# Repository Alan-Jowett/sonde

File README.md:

<!-- SPDX-License-Identifier: MIT
  Copyright (c) 2026 sonde contributors -->

# Sonde

**A programmable sensor platform with desired-state convergence from cloud to node.**

Sonde turns battery-powered sensor nodes into programmable probes that keep static firmware but execute dynamic behavior defined by verified BPF programs ([RFC 9669](https://www.rfc-editor.org/rfc/rfc9669.html)). The gateway owns radio-facing orchestration; an external control plane owns fleet intent. Together they converge node state by flowing **desired state** down to the gateway and **actual state / application data** back upstream.

Nodes never need feature-driven firmware updates for normal application changes. New sampling logic, thresholds, diagnostics, and routing behavior ship as verified BPF plus gateway-managed state changes. The reference implementation targets ESP32-C3/S3 nodes and modems, with a cloud-agnostic connector model and an Azure reference deployment in this repository.

> **Status:** Active development, pre-1.0. The workspace includes the core protocol/gateway/node/modem stack, admin tooling, pairing surfaces, example handlers, and Azure companion/handler components. See [Project status](#project-status) below.

> ⚠️ **Spec-first project** — edit the [specification documents](docs/) before changing code. Code modules may be regenerated from specs. See [Contributing](docs/contributing.md#spec-first-development-model).

---

## Project status

**Lifecycle:** Active development — pre-1.0. APIs and wire formats may change between commits. Not yet recommended for production deployments.

**Maintenance:** The project is actively maintained. Bug reports, pull requests, and feature discussions are welcome. See [Contributing](docs/contributing.md) for guidelines.

**Versioning:** The project has not yet reached v1.0. Breaking changes to the wire protocol, connector schema, or crate APIs may still occur.

**Current repository shape:** the workspace already spans the device runtime, the gateway runtime, local admin/pairing tools, and cloud-facing integration surfaces.

| Component | Purpose |
|---|---|
| [`sonde-protocol`](crates/sonde-protocol) | Shared `no_std` wire format, CBOR message types, program-image encoding, and crypto abstractions |
| [`sonde-gateway`](crates/sonde-gateway) | Async gateway service: node sessions, program distribution, reconciliation hooks, connector I/O, and gRPC admin |
| [`sonde-node`](crates/sonde-node) | ESP32-C3/S3 firmware: wake cycle, BPF execution, persistent state, and radio protocol |
| [`sonde-modem`](crates/sonde-modem) | ESP32-S3 bridge between ESP-NOW radio and the gateway |
| [`sonde-admin`](crates/sonde-admin) | CLI for gateway administration and pairing flows |
| [`sonde-bpf`](crates/sonde-bpf) | Safe BPF interpreter used by the node runtime |
| [`sonde-pair`](crates/sonde-pair) + [`sonde-pair-ui`](crates/sonde-pair-ui/src-tauri) | BLE pairing core plus Tauri desktop/Android UI |
| [`sonde-azure-companion`](crates/sonde-azure-companion) | Reference connector/runtime bridge for Azure-backed control-plane sync |
| [`sonde-azure-handler`](crates/sonde-azure-handler) | Azure cloud-side reconciliation and data-ingest component |
| [`sonde-tmp102-handler`](crates/sonde-tmp102-handler) / [`sonde-sht40-handler`](crates/sonde-sht40-handler) | Example application handlers |
| [`sonde-e2e`](crates/sonde-e2e) | End-to-end validation harness |

CI runs on every push and PR and covers workspace build/test flows plus target-specific firmware and UI pipelines.

---

## How it works

```
┌───────────────────────────┐
│   Control plane / cloud   │
│ desired state, analytics, │
│ fleet policy, app ingest  │
└─────────────┬─────────────┘
              │ DESIRED_STATE / ACTUAL_STATE / APP_DATA
┌─────────────▼─────────────┐     local IPC      ┌──────────┐     USB      ┌──────────┐   ESP-NOW   ┌──────────┐
│ Connector / companion     │◄──────────────────►│ Gateway  │◄────────────►│  Modem   │◄───────────►│   Node   │
│ transport adapter         │                    │          │               │          │              │  BPF VM  │
└───────────────────────────┘                    └──────────┘               └──────────┘              └──────────┘
```

1. **The control plane declares intent** as complete desired state for one gateway or node at a time.
2. **A connector/companion transports that intent** to the gateway over the local connector API. The connector is cloud-agnostic; it adapts some external store-and-forward transport to Sonde's framed connector messages.
3. **Nodes wake on their own schedule** and send `WAKE` over ESP-NOW. Communication is always node-initiated.
4. **The gateway reconciles actual vs. desired state** at wake time, then responds with the next action: continue, update resident program, queue an ephemeral diagnostic, change schedule, rotate state, or reboot.
5. **The node executes its resident BPF program**, updates persistent maps, and emits application data when needed.
6. **The gateway publishes upstream actual state and app data** so the control plane can observe convergence and decide the next desired state.

The firmware never embeds application-specific policy. It provides the execution and transport substrate; BPF plus desired-state convergence define behavior.

---

## Architecture

The design separates five concerns:

| Layer | Lifetime | Location |
|---|---|---|
| **Firmware** | Static, uniform across all nodes | Flash |
| **Program logic** | Dynamic, delivered as BPF bytecode | Flash (resident) or RAM (ephemeral) |
| **Persistent state** | Survives deep sleep | Sleep-persistent memory |
| **Gateway runtime** | Always-on edge service | Gateway host |
| **Control plane** | External desired-state authority | Cloud or other upstream system |

This gives Sonde OTA-like flexibility without turning firmware rollout into the main application-delivery mechanism. New sensors, thresholds, schedules, diagnostics, and cloud-side routing changes are expressed as BPF programs plus desired state.

### Desired-state convergence

The connector protocol is organized around four message families:

- **`DESIRED_STATE`** — control plane to gateway, carrying complete desired state for one gateway or node.
- **`ACTUAL_STATE`** — gateway to control plane, carrying the latest observed gateway or node state.
- **`APP_DATA`** — gateway to control plane, carrying node-originated application payloads.
- **`CONNECTOR_HEALTH`** — gateway to control plane, carrying connector session health.

This makes the gateway the convergence engine at the edge: it accepts desired state from upstream, waits for node-initiated contact, applies the necessary changes, and reports the resulting actual state back upstream.

### Reference cloud deployment

This repository's reference cloud path is Azure-based:

- `sonde-azure-companion` bridges the gateway's local admin/connector surfaces to Azure runtime services.
- `sonde-azure-handler` consumes upstream connector traffic, stores actual state and sensor data, and emits downstream desired state.

The connector model itself is not Azure-specific, so other control-plane transports can implement the same gateway-facing contract.

---

## BPF programs

Nodes execute [BPF programs](docs/bpf-environment.md) that define all application behavior. Two classes exist:

- **Resident** — stored in flash, runs every wake cycle, full map read/write access.
- **Ephemeral** — one-shot diagnostic, stored in RAM, read-only maps, discarded after execution.

Programs are compiled to BPF ELF, verified by [Prevail](https://github.com/vbpf/ebpf-verifier) on the gateway, and distributed over the air. See the [BPF environment](docs/bpf-environment.md) doc for the full helper API, memory model, verification profiles, and development workflow.

---

## Radio protocol and security

Communication is always **node-initiated**. The gateway never wakes a node. Each radio frame uses:

- a fixed **11-byte binary header** (`key_hint`, `msg_type`, `nonce`),
- a CBOR payload encrypted with **AES-256-GCM**, and
- a 16-byte GCM authentication tag.

The header is authenticated as AEAD additional data; the payload is both encrypted and authenticated. Nodes and gateways use unique per-node 256-bit pre-shared keys. `WAKE` uses a random nonce; follow-on traffic uses gateway-assigned sequence numbers for replay protection.

The basic edge loop is still: node sends `WAKE` → gateway responds with `COMMAND` → node executes BPF → node sleeps. Programs are distributed via a node-driven chunked transfer. Application data flows as `APP_DATA`, with `APP_DATA_REPLY` used for request/response helper calls.

See [protocol.md](docs/protocol.md) for the full wire format and [security.md](docs/security.md) for the trust model.

### Security model

- Each node has a unique 256-bit pre-shared key stored in a dedicated flash partition.
- Keys are provisioned via USB-mediated pairing; no over-the-air key exchange.
- The gateway stores the key database and authenticates/decrypts all radio traffic with AES-256-GCM.
- Nonces provide replay protection for WAKE; gateway-assigned sequence numbers protect all subsequent messages.
- BPF programs are integrity-checked by content hash at every transfer.
- Nodes can be factory-reset (erasing key, maps, and program) and re-paired with a fresh identity.

See [security.md](docs/security.md) for the complete security model: threat model, key provisioning, authentication, replay protection, identity binding, failure modes, and gateway failover.

---

## BPF program environment

BPF programs have access to raw bus primitives (I2C, SPI, GPIO, ADC), communication helpers (`send`, `send_recv`), persistent maps, and system functions. The firmware provides bus access; sensor-specific protocols live in the BPF program. See [bpf-environment.md](docs/bpf-environment.md) for the full helper API, memory model, verification profiles, and development workflow.

---

## Application handlers

The gateway is a platform service — application logic runs in a separate **handler process**. When a BPF program calls `send()` or `send_recv()`, the gateway forwards the data to the handler via stdin (length-prefixed CBOR). The handler processes it and replies via stdout. Handlers are routed by `program_hash`, so different BPF programs can have different handlers.

The developer ships two artifacts: a **BPF ELF** (node-side) and a **handler** in any language (gateway-side). See [gateway-api.md](docs/gateway-api.md) for the full handler protocol, message format, and examples.

---

## Operational concerns

- **Gateway failover** — replace the gateway with another instance provisioned with the same key database. Nodes won't notice.
- **Development** — BPF programs are platform-agnostic. Compile, verify, and test locally with `libsonde_test` — no hardware needed.
- **Diagnostics** — push an ephemeral program to inspect node state without disturbing the resident program.
- **Firmware updates** — physical access only. By design, firmware changes are rare — new features ship as BPF programs.

See [gateway-requirements.md](docs/gateway-requirements.md) and [node-requirements.md](docs/node-requirements.md) for formal requirements.

---

## Example use cases

All implemented as BPF programs, not firmware changes:

- *"Increase sampling frequency for the next 10 minutes."*
- *"Dump all persistent map contents for diagnostics."*
- *"Recalibrate soil sensor thresholds."*
- *"Send an immediate alert if temperature exceeds 35°C."*
- *"Run anomaly detection locally and only transmit deltas."*

---

## Reference implementation: ESP32-C3/S3

The reference implementation targets ESP32-C3 (RISC-V) and ESP32-S3 (Xtensa) running ESP-IDF.

| Aspect | Detail |
|---|---|
| **Radio transport** | ESP-NOW — connectionless 802.11, 250-byte frames (~207 bytes payload after auth overhead) |
| **Sleep-persistent memory** | RTC slow SRAM: 8 KB on C3, 8+8 KB on S3 (~4–6 KB usable for maps) |
| **Key storage** | Dedicated flash partition (software-accessible; security depends on secure boot / flash encryption; key erased on factory reset) |
| **Hardware crypto** | SHA-256, HMAC-SHA256, AES-128/256, hardware RNG (~10x faster than software) |
| **RAM** | C3: 400 KB (16 KB cache). S3: 512 KB |
| **Flash endurance** | ~100K erase cycles per 4 KB sector (273+ years at 1 update/day) |
| **BPF execution** | Interpreter only (`sonde-bpf`, RFC 9669 compliant; no JIT for RISC-V/Xtensa). The `BpfInterpreter` trait allows alternative backends (e.g., rbpf, uBPF) to be plugged in. |
| **Max program size** | 4 KB resident, 2 KB ephemeral (recommended) |
| **Chunked transfer** | 4 KB program ≈ 20 round-trips over ESP-NOW |

### Canonical contributor hardware

Contributor-facing hardware docs and bring-up notes should assume these baseline builds unless a document explicitly says otherwise:

| Build | Base hardware | Notes |
|---|---|---|
| **Node** | [`hw/carrier-board`](hw/carrier-board) + Seeed Studio XIAO ESP32-C3 | Canonical battery-powered node build. The carrier board provides the Qwiic/I2C sensor connector and battery input. |
| **Modem** | [`hw/carrier-board`](hw/carrier-board) + Seeed Studio XIAO ESP32-S3 | Canonical USB modem build. Add a 128×64 SSD1306-compatible OLED on I2C0 (`GPIO5` SDA, `GPIO6` SCL, address `0x3C`) and an active-low button on `GPIO2`. |

---

## Building

```sh
# Fast protocol-only test
cargo test -p sonde-protocol

# Validate the workspace
cargo build --workspace
cargo clippy --workspace -- -D warnings
cargo test --workspace
```

Building the modem firmware requires the ESP-IDF Xtensa toolchain:

```sh
# Linux / macOS
. "$HOME/export-esp.sh"
cargo +esp build -p sonde-modem --features esp --target xtensa-esp32s3-espidf -Zbuild-std=std,panic_abort
```

```powershell
# Windows (PowerShell)
. ~/export-esp.ps1
cargo +esp build -p sonde-modem --features esp --target xtensa-esp32s3-espidf -Zbuild-std=std,panic_abort
```

See [Getting Started](docs/getting-started.md) for full toolchain setup.

---

## Further reading

- [Overview](docs/overview.md) — project summary, status, and goals
- [Getting Started](docs/getting-started.md) — developer environment setup, toolchain installation, build and flash commands
- [Node BOM](docs/node-bom.md) — canonical carrier-board + XIAO ESP32-C3 node build
- [Modem BOM](docs/modem-bom.md) — canonical carrier-board + XIAO ESP32-S3 modem build with local display/button
- [Contributing](docs/contributing.md) — contribution guidelines, DCO, SPDX requirements
- [Why BPF?](docs/why-bpf.md) — rationale for using BPF + Prevail as the execution model
- [BPF Environment](docs/bpf-environment.md) — program API, memory model, verification, and development workflow
- [Application API](docs/gateway-api.md) — data-plane API for building applications on the Sonde platform
- [Connector API](docs/gateway-companion-api.md) — desired-state / actual-state integration API for external control planes
- [Protocol](docs/protocol.md) — node-gateway wire protocol specification
- [Gateway Requirements](docs/gateway-requirements.md) — formal gateway requirements
- [Node Requirements](docs/node-requirements.md) — formal node firmware requirements
- [Security Model](docs/security.md) — threat model, key provisioning, authentication, replay protection, and failure modes
- [Azure Companion Requirements](docs/azure-companion-requirements.md) — Azure reference deployment for control-plane sync
- [Azure Provisioning Requirements](docs/azure-provisioning-requirements.md) — Bicep/bootstrap contract for the Azure deployment

---

## Related Work

Prior work has explored the use of eBPF‑derived virtual machines on microcontroller‑class devices to enable safe, dynamically deployable software modules. **Femto‑Containers** and **rBPF** integrate a reduced eBPF virtual machine into [RIOT‑OS](https://www.riot-os.org/), allowing small sandboxed programs to be deployed and executed on low‑power IoT devices, primarily to support DevOps‑style updates and fault isolation without reflashing firmware. These systems demonstrate that an eBPF‑like instruction set can be executed efficiently on resource‑constrained hardware and safely isolated from the host OS. Key references include:
- [Femto‑Containers paper](https://arxiv.org/abs/2106.12553)
- [Femto‑Containers code](https://github.com/future-proof-iot/Femto-Container)
- [rBPF paper](https://arxiv.org/abs/2011.12047)

Subsequent work, including **μBPF**, extends this line of research with just‑in‑time (JIT) compilation, over‑the‑air deployment pipelines, and formal verification to improve performance and provide stronger correctness guarantees for eBPF execution on microcontrollers. Key references include:
- [μBPF paper](https://marioskogias.github.io/docs/microbpf.pdf)
- [μBPF code](https://github.com/SzymonKubica/micro-bpf)

**rbpf** is a pure‑Rust user‑space eBPF interpreter (and optional JIT) that demonstrates BPF execution outside the Linux kernel in a safe, portable runtime:
- [rbpf code](https://github.com/qmonnet/rbpf)

Related efforts also focus on formally verified eBPF interpreters and JITs for RIOT‑based systems, emphasizing proof‑carrying safety and memory isolation rather than general application architecture. See also:
- [End‑to‑end mechanized proof of rBPF](https://link.springer.com/chapter/10.1007/978-3-031-65627-9_16)

In contrast to these systems, which primarily treat eBPF as a *mechanism* for hosting isolated application fragments within a general‑purpose embedded operating system, **Sonde** adopts BPF as the *primary application execution model*. Sonde intentionally freezes node firmware and delegates all application behavior—including sampling logic, thresholds, diagnostics, and scheduling—to verified BPF bytecode managed by a gateway‑driven control plane. This design emphasizes end‑to‑end behavioral control, predictable energy usage, and verification‑first safety guarantees, rather than OS extensibility, multi‑tenant execution, or embedded DevOps tooling.

---

## Contributing

See [docs/contributing.md](docs/contributing.md) for full guidelines.

All contributions must include:

1. **SPDX license headers** — every `.md` and `.rs` file must start with:

   *Markdown:*
   ```
   <!-- SPDX-License-Identifier: MIT
     Copyright (c) 2026 sonde contributors -->
   ```
   *Rust:*
   ```rust
   // SPDX-License-Identifier: MIT
   // Copyright (c) 2026 sonde contributors
   ```

2. **DCO sign-off** — every commit must include a `Signed-off-by:` trailer (use `git commit -s`).

Install the repository's git hooks so these rules are enforced locally:

```sh
git config core.hooksPath hooks
```

Alternatively, if you use the [pre-commit](https://pre-commit.com) framework:

```sh
pip install pre-commit
pre-commit install --hook-type pre-commit --hook-type commit-msg
```

---

## License

[MIT](LICENSE)

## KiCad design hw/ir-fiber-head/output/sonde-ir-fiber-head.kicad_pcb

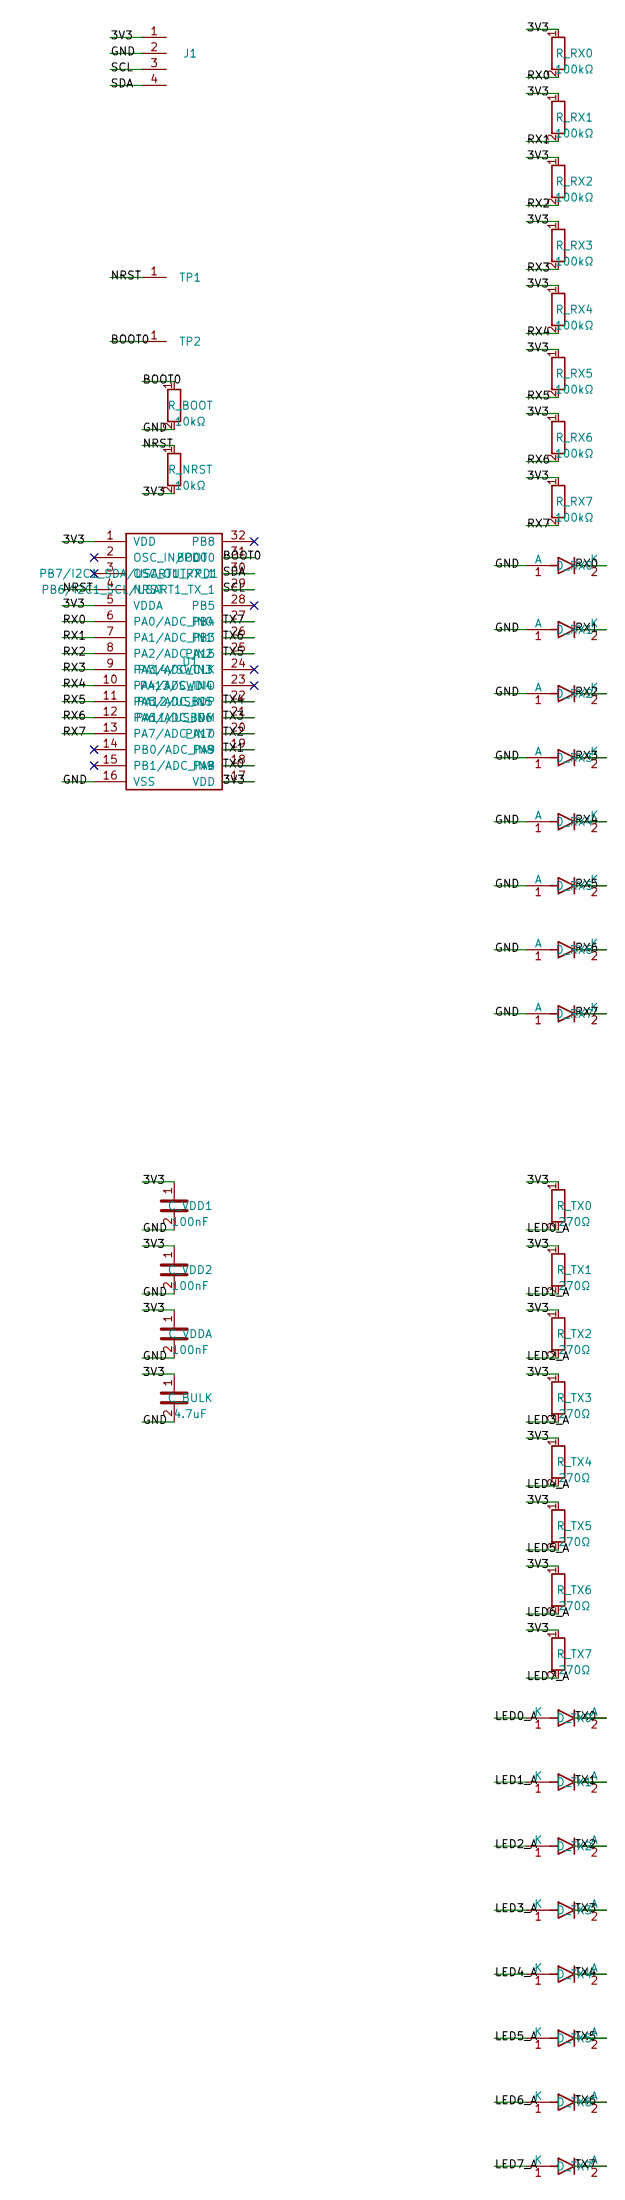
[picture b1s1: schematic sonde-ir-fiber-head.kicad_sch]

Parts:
C_BULK: 4.7uF; C_0603_1608Metric
C_VDD1, C_VDD2: 100nF; C_0603_1608Metric
C_VDDA: 100nF; C_0603_1608Metric
D_RX0, D_RX1, D_RX2, D_RX3, D_RX4, D_RX5, D_RX6, D_RX7: Photodiode_D3.0mm_P2.54mm_Fiber1.00mm_UpsideDown
D_TX0, D_TX1, D_TX2, D_TX3, D_TX4, D_TX5, D_TX6, D_TX7: LED_D3.0mm_P2.54mm_Fiber1.00mm_UpsideDown
J1: WirePad_1x04_P2.54mm_D1.0mm
R_BOOT: 10kΩ; R_0603_1608Metric
R_NRST: 10kΩ; R_0603_1608Metric
R_RX0, R_RX1, R_RX2, R_RX3, R_RX4, R_RX5, R_RX6, R_RX7: 100kΩ; R_0603_1608Metric
R_TX0, R_TX1, R_TX2, R_TX3, R_TX4, R_TX5, R_TX6, R_TX7: 270Ω; R_0603_1608Metric
TP1, TP2: TestPoint_THTPad_D1.5mm_Drill0.7mm
U1: LQFP-32_7x7mm_P0.8mm

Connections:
3V3: C_BULK.1, C_VDD1.1, C_VDD2.1, C_VDDA.1, J1.1, R_NRST.2, R_RX0.1, R_RX1.1, R_RX2.1, R_RX3.1, R_RX4.1, R_RX5.1, R_RX6.1, R_RX7.1, R_TX0.1, R_TX1.1, R_TX2.1, R_TX3.1, R_TX4.1, R_TX5.1, R_TX6.1, R_TX7.1, U1.1 (VDD), U1.5 (VDDA), U1.17 (VDD)
BOOT0: R_BOOT.1, TP2.1, U1.31 (BOOT0)
GND: C_BULK.2, C_VDD1.2, C_VDD2.2, C_VDDA.2, D_RX0.1 (A), D_RX1.1 (A), D_RX2.1 (A), D_RX3.1 (A), D_RX4.1 (A), D_RX5.1 (A), D_RX6.1 (A), D_RX7.1 (A), J1.2, R_BOOT.2, U1.16 (VSS)
LED0_A: D_TX0.1 (K), R_TX0.2
LED1_A: D_TX1.1 (K), R_TX1.2
LED2_A: D_TX2.1 (K), R_TX2.2
LED3_A: D_TX3.1 (K), R_TX3.2
LED4_A: D_TX4.1 (K), R_TX4.2
LED5_A: D_TX5.1 (K), R_TX5.2
LED6_A: D_TX6.1 (K), R_TX6.2
LED7_A: D_TX7.1 (K), R_TX7.2
NRST: R_NRST.1, TP1.1, U1.4 (NRST)
RX0: D_RX0.2 (K), R_RX0.2, U1.6 (PA0/ADC_IN0)
RX1: D_RX1.2 (K), R_RX1.2, U1.7 (PA1/ADC_IN1)
RX2: D_RX2.2 (K), R_RX2.2, U1.8 (PA2/ADC_IN2)
RX3: D_RX3.2 (K), R_RX3.2, U1.9 (PA3/ADC_IN3)
RX4: D_RX4.2 (K), R_RX4.2, U1.10 (PA4/ADC_IN4)
RX5: D_RX5.2 (K), R_RX5.2, U1.11 (PA5/ADC_IN5)
RX6: D_RX6.2 (K), R_RX6.2, U1.12 (PA6/ADC_IN6)
RX7: D_RX7.2 (K), R_RX7.2, U1.13 (PA7/ADC_IN7)
SCL: J1.3, U1.29 (PB6/I2C1_SCL/USART1_TX_1)
SDA: J1.4, U1.30 (PB7/I2C1_SDA/USART1_RX_1)
TX0: D_TX0.2 (A), U1.18 (PA8)
TX1: D_TX1.2 (A), U1.19 (PA9)
TX2: D_TX2.2 (A), U1.20 (PA10)
TX3: D_TX3.2 (A), U1.21 (PA11/USBDM)
TX4: D_TX4.2 (A), U1.22 (PA12/USBDP)
TX5: D_TX5.2 (A), U1.25 (PA15)
TX6: D_TX6.2 (A), U1.26 (PB3)
TX7: D_TX7.2 (A), U1.27 (PB4)

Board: 2 copper layers, 42 parts (0 on the bottom side), 30 nets, no tracks yet.

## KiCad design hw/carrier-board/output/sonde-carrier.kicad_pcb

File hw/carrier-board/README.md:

<!-- SPDX-License-Identifier: MIT
  Copyright (c) 2026 sonde contributors -->
# Sonde Carrier Board — Manufacturing Guide

## Overview

The sonde carrier board is a 2-layer PCB that hosts a Seeed Studio XIAO module and
provides connectors for I2C (Qwiic), 1-Wire sensors, and a 2×AA lithium battery
pack. The board powers the MCU directly from the battery (no LDO) and includes a
P-FET load switch for gating sensor power during deep sleep.

This board is the canonical base PCB for both contributor reference builds:

- **Node:** carrier board + Seeed Studio XIAO ESP32-C3
- **Modem:** carrier board + Seeed Studio XIAO ESP32-S3, plus an SSD1306-compatible
  128×64 OLED on `GPIO5`/`GPIO6` (`0x3C`) and an active-low button on `GPIO2`

**Carrier board deep sleep current (excluding the XIAO module): ~0.01 µA** (essentially zero).

## Prerequisites

- [KiCad 8](https://www.kicad.org/download/) (free, open-source EDA)
- A [JLCPCB](https://jlcpcb.com/) account (or compatible PCB fab)
- A Seeed Studio XIAO ESP32-C3 or Seeed Studio XIAO ESP32-S3 module (not included in this BOM)

## Directory Contents

| File | Description |
|------|-------------|
| `ir/` | Intermediate Representation YAML files (IR-0 through IR-3) |
| `bom-jlcpcb.csv` | Bill of Materials in JLCPCB format |
| `cpl-jlcpcb.csv` | Component Placement List (header only — coordinates populated after layout) |
| `README.md` | This file |

KiCad project files (`.kicad_pro`, `.kicad_sch`, `.kicad_pcb`) will be
generated by the `sonde-kicad` tool from the IR files.

## How to Order PCBs

### Step 1: Generate KiCad Files

1. Run `sonde-kicad build --ir-dir hw/carrier-board/ir/` to generate
   the schematic and PCB layout from IR files.
2. Open the generated `.kicad_sch` and `.kicad_pcb` in KiCad 8 to review.

### Step 2: Generate Gerber Files

1. In the PCB editor: File → Fabrication Outputs → Gerbers (.gbr)
2. Set output directory to `gerbers/`
3. Select layers: F.Cu, B.Cu, F.SilkS, B.SilkS, F.Mask, B.Mask, Edge.Cuts
4. Click "Plot"
5. Then: File → Fabrication Outputs → Drill Files (.drl)
6. Generate drill file to the same `gerbers/` directory

### Step 3: Upload to JLCPCB

1. Go to [jlcpcb.com](https://jlcpcb.com/) and click "Order Now"
2. Upload the Gerber ZIP file
3. Set PCB parameters:
   - Layers: 2
   - PCB Thickness: 1.6 mm
   - Surface Finish: HASL (lead-free)
   - Copper Weight: 1 oz
4. Enable "SMT Assembly" if you want JLCPCB to solder SMD parts
5. Upload `bom-jlcpcb.csv` as the BOM
6. Upload `cpl-jlcpcb.csv` as the CPL (coordinates filled in after layout)

### Step 4: Hand-Solder Through-Hole Parts

JLCPCB SMT assembly handles the SMD components (resistors, caps, MOSFET,
JST SH connectors). The following through-hole parts need hand soldering:

- **J2** — JST XH 3-pin (1-Wire connector)
- **J3** — JST PH 2-pin (battery connector)
- **J6, J7** — 1×7 female pin headers (XIAO socket)

Use a soldering iron at 350°C with lead-free solder.

### Step 5: Insert the XIAO Module

1. Solder pin headers onto the XIAO ESP32-C3 (if not pre-soldered)
2. Insert the XIAO into J6/J7 with the **USB-C port facing outward**
   and the **antenna toward the top edge** of the carrier board
3. The XIAO should plug in snugly — no soldering needed on the carrier side

## Schematic Summary

```
VBAT (2×AA lithium, JST PH) ──┬──[C3 10µF]── GND
                               │
                               ├──► XIAO 3V3 pin (direct, no regulator)
                               │
                               ├──[R4 100kΩ]──┬── Q1 Gate (Si2301 P-FET)
                               │              │
                               │         GPIO4 (SENSOR_EN)
                               │
                               └──► Q1 Source
                                    Q1 Drain ──► SENSOR_V rail
                                                    │
                                    ┌───────────────┼────────────┐
                                    │               │            │
                                 [R1,R2 4.7kΩ]  [R3 4.7kΩ]  [R5,R6 100kΩ]
                                    │               │            │
                                 SDA,SCL          1-Wire DQ    VBAT_SENSE
                                 (GPIO6,7)        (GPIO3)      (GPIO2 ADC)
                                    │               │
                                 J1 Qwiic        J2 JST XH
```

## BOM Cost (qty 100)

| Item | Cost |
|------|------|
| PCB fabrication | ~$0.25/board |
| SMD components | ~$0.86/board |
| JLCPCB assembly | ~$0.80/board |
| **Total (carrier board only)** | **~$1.91/board** |
| XIAO ESP32-C3 (user-supplied) | ~$5.00 |

## Design Documents

- Manufacturing and assembly guidance: this document (`hw/carrier-board/README.md`)
- Hardware design sources: IR files in `hw/carrier-board/ir/`

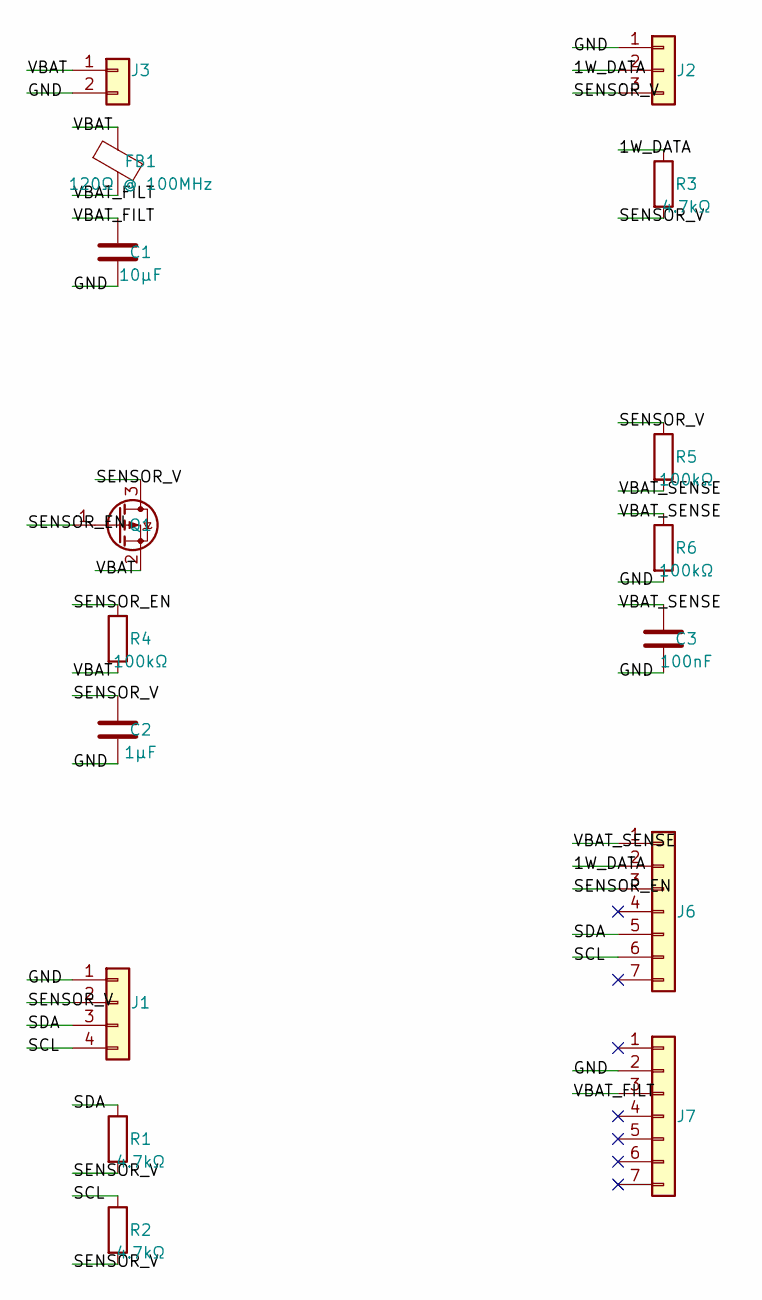
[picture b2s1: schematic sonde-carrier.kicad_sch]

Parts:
C1: 10µF; C_0805_2012Metric
C2: 1µF; C_0402_1005Metric
C3: 100nF; C_0402_1005Metric
FB1: 120Ω @ 100MHz; L_0402_1005Metric
J1: JST_SH_SM04B-SRSS-TB_1x04-1MP_P1.00mm_Horizontal
J2: JST_PH_S3B-PH-K_1x03_P2.00mm_Horizontal
J3: JST_PH_S2B-PH-K_1x02_P2.00mm_Horizontal
J6, J7: PinSocket_1x07_P2.54mm_Vertical
Q1: SOT-23
R1, R2, R3: 4.7kΩ; R_0402_1005Metric
R4, R5, R6: 100kΩ; R_0402_1005Metric

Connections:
1W_DATA: J2.2, J6.2, R3.1
GND: C1.2, C2.2, C3.2, J1.1, J2.1, J3.2, J7.2, R6.2
SCL: J1.4, J6.6, R2.1
SDA: J1.3, J6.5, R1.1
SENSOR_EN: J6.3, Q1.1 (G), R4.1
SENSOR_V: C2.1, J1.2, J2.3, Q1.3 (D), R1.2, R2.2, R3.2, R5.1
VBAT: FB1.1, J3.1, Q1.2 (S), R4.2
VBAT_FILT: C1.1, FB1.2, J7.3
VBAT_SENSE: C3.1, J6.1, R5.2, R6.1

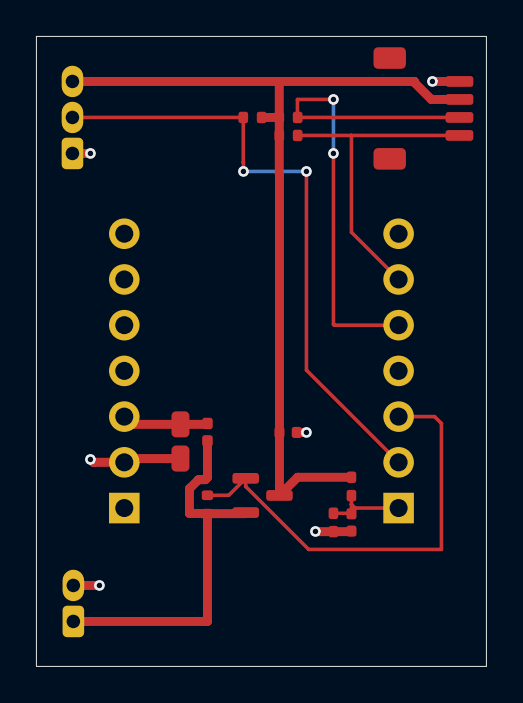
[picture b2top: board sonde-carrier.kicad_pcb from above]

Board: 2 copper layers, 25.0 x 35.0 mm, 16 parts (0 on the bottom side), 9 nets.

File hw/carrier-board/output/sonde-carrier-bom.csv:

Designator,Value,Footprint,Manufacturer,Part Number,LCSC Part Number,Quantity
C1,10µF,Capacitor_SMD:C_0805_2012Metric,Samsung,CL21A106KAYNNNE,C15850,1
C2,1µF,Capacitor_SMD:C_0402_1005Metric,Samsung,CL05A105KA5NQNC,C52923,1
C3,100nF,Capacitor_SMD:C_0402_1005Metric,YAGEO,CC0402KRX7R7BB104,C307331,1
FB1,120Ω @ 100MHz,Inductor_SMD:L_0402_1005Metric,Murata,BLM15AG121SN1D,C85812,1
J1,~,Connector_JST:JST_SH_SM04B-SRSS-TB_1x04-1MP_P1.00mm_Horizontal,JST,SM04B-SRSS-TB(LF)(SN),C160404,1
J2,~,Connector_JST:JST_PH_S3B-PH-K_1x03_P2.00mm_Horizontal,JST,S3B-PH-K-S(LF)(SN),C157929,1
J3,~,Connector_JST:JST_PH_S2B-PH-K_1x02_P2.00mm_Horizontal,JST,S2B-PH-K-S(LF)(SN),C157932,1
J6,~,Connector_PinSocket_2.54mm:PinSocket_1x07_P2.54mm_Vertical,Generic,1×7 Female Header 2.54mm,—,1
J7,~,Connector_PinSocket_2.54mm:PinSocket_1x07_P2.54mm_Vertical,Generic,1×7 Female Header 2.54mm,—,1
Q1,~,Package_TO_SOT_SMD:SOT-23,Vishay Siliconix,Si2301CDS-T1-GE3,C10487,1
R1,4.7kΩ,Resistor_SMD:R_0402_1005Metric,Uniroyal,0402WGF4701TCE,C25900,1
R2,4.7kΩ,Resistor_SMD:R_0402_1005Metric,Uniroyal,0402WGF4701TCE,C25900,1
R3,4.7kΩ,Resistor_SMD:R_0402_1005Metric,Uniroyal,0402WGF4701TCE,C25900,1
R4,100kΩ,Resistor_SMD:R_0402_1005Metric,Uniroyal,0402WGF1003TCE,C25741,1
R5,100kΩ,Resistor_SMD:R_0402_1005Metric,Uniroyal,0402WGF1003TCE,C25741,1
R6,100kΩ,Resistor_SMD:R_0402_1005Metric,Uniroyal,0402WGF1003TCE,C25741,1

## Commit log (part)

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2026-06-04 deps: Bump log from 0.4.30 to 0.4.31 (#1124)
    Bumps [log](https://github.com/rust-lang/log) from 0.4.30 to 0.4.31.
    - [Release notes](https://github.com/rust-lang/log/releases)
    - [Changelog](https://github.com/rust-lang/log/blob/master/CHANGELOG.md)
    - [Commits](https://github.com/rust-lang/log/compare/0.4.30...0.4.31)
    ---
    updated-dependencies:
2026-06-04 deps: Bump rpassword from 7.5.3 to 7.5.4 (#1125)
    Bumps [rpassword](https://github.com/conradkleinespel/rpassword) from 7.5.3 to 7.5.4.
    - [Release notes](https://github.com/conradkleinespel/rpassword/releases)
    - [Commits](https://github.com/conradkleinespel/rpassword/compare/v7.5.3...v7.5.4)
    ---
    updated-dependencies:
    - dependency-name: rpassword
2026-06-04 deps: Bump getrandom from 0.3.4 to 0.4.2 (#1121)
    Bumps [getrandom](https://github.com/rust-random/getrandom) from 0.3.4 to 0.4.2.
    - [Changelog](https://github.com/rust-random/getrandom/blob/master/CHANGELOG.md)
    - [Commits](https://github.com/rust-random/getrandom/compare/v0.3.4...v0.4.2)
    ---
    updated-dependencies:
    - dependency-name: getrandom
2026-06-10 deps: Bump prost from 0.14.3 to 0.14.4 in the grpc group
    Bumps the grpc group with 1 update: [prost](https://github.com/tokio-rs/prost).
    Updates `prost` from 0.14.3 to 0.14.4
    - [Release notes](https://github.com/tokio-rs/prost/releases)
    - [Changelog](https://github.com/tokio-rs/prost/blob/master/CHANGELOG.md)
    - [Commits](https://github.com/tokio-rs/prost/compare/v0.14.3...v0.14.4)
    ---
2026-06-10 deps: Bump rusqlite from 0.39.0 to 0.40.1
    Bumps [rusqlite](https://github.com/rusqlite/rusqlite) from 0.39.0 to 0.40.1.
    - [Release notes](https://github.com/rusqlite/rusqlite/releases)
    - [Changelog](https://github.com/rusqlite/rusqlite/blob/master/Changelog.md)
    - [Commits](https://github.com/rusqlite/rusqlite/compare/v0.39.0...v0.40.1)
    ---
    updated-dependencies:
2026-06-10 deps: Bump uuid from 1.23.2 to 1.23.3
    Bumps [uuid](https://github.com/uuid-rs/uuid) from 1.23.2 to 1.23.3.
    - [Release notes](https://github.com/uuid-rs/uuid/releases)
    - [Commits](https://github.com/uuid-rs/uuid/compare/v1.23.2...v1.23.3)
    ---
    updated-dependencies:
    - dependency-name: uuid
2026-06-10 deps: Bump chrono from 0.4.44 to 0.4.45
    Bumps [chrono](https://github.com/chronotope/chrono) from 0.4.44 to 0.4.45.
    - [Release notes](https://github.com/chronotope/chrono/releases)
    - [Changelog](https://github.com/chronotope/chrono/blob/main/CHANGELOG.md)
    - [Commits](https://github.com/chronotope/chrono/compare/v0.4.44...v0.4.45)
    ---
    updated-dependencies:
2026-06-13 deps: Bump prost from 0.14.3 to 0.14.4 in the grpc group (#1130)
    Bumps the grpc group with 1 update: [prost](https://github.com/tokio-rs/prost).
    Updates `prost` from 0.14.3 to 0.14.4
    - [Release notes](https://github.com/tokio-rs/prost/releases)
    - [Changelog](https://github.com/tokio-rs/prost/blob/master/CHANGELOG.md)
    - [Commits](https://github.com/tokio-rs/prost/compare/v0.14.3...v0.14.4)
    ---
2026-06-13 deps: Bump log from 0.4.31 to 0.4.32 (#1132)
    Bumps [log](https://github.com/rust-lang/log) from 0.4.31 to 0.4.32.
    - [Release notes](https://github.com/rust-lang/log/releases)
    - [Changelog](https://github.com/rust-lang/log/blob/master/CHANGELOG.md)
    - [Commits](https://github.com/rust-lang/log/compare/0.4.31...0.4.32)
    ---
    updated-dependencies:
2026-06-13 deps: Bump uuid from 1.23.2 to 1.23.3 (#1133)
    Bumps [uuid](https://github.com/uuid-rs/uuid) from 1.23.2 to 1.23.3.
    - [Release notes](https://github.com/uuid-rs/uuid/releases)
    - [Commits](https://github.com/uuid-rs/uuid/compare/v1.23.2...v1.23.3)
    ---
    updated-dependencies:
    - dependency-name: uuid
2026-06-17 deps: Bump time from 0.3.47 to 0.3.49
    Bumps [time](https://github.com/time-rs/time) from 0.3.47 to 0.3.49.
    - [Release notes](https://github.com/time-rs/time/releases)
    - [Changelog](https://github.com/time-rs/time/blob/main/CHANGELOG.md)
    - [Commits](https://github.com/time-rs/time/compare/v0.3.47...v0.3.49)
    ---
    updated-dependencies:
2026-06-17 deps: Bump regex from 1.12.3 to 1.12.4
    Bumps [regex](https://github.com/rust-lang/regex) from 1.12.3 to 1.12.4.
    - [Release notes](https://github.com/rust-lang/regex/releases)
    - [Changelog](https://github.com/rust-lang/regex/blob/master/CHANGELOG.md)
    - [Commits](https://github.com/rust-lang/regex/compare/1.12.3...1.12.4)
    ---
    updated-dependencies:
2026-06-17 deps: Bump zeroize from 1.8.2 to 1.9.0
    Bumps [zeroize](https://github.com/RustCrypto/utils) from 1.8.2 to 1.9.0.
    - [Commits](https://github.com/RustCrypto/utils/compare/zeroize-v1.8.2...zeroize-v1.9.0)
    ---
    updated-dependencies:
    - dependency-name: zeroize
    dependency-version: 1.9.0
2026-06-17 feat(web-ui): add Custom Dashboards with computed metrics
    Add Custom Dashboards feature allowing admins to create multi-dashboard views with
    algebraic expressions over sensor data.
    Requirements (WEB-1100 through WEB-1110):
    - Dashboard CRUD operations with tab navigation
    - Variable binding to sensor data sources (node ID + reading type)
    - Expression editor with safe evaluation (expr-eval 2.0.2, no eval())
2026-06-17 Add adversarial-branch-review
2026-06-17 Fix code review round 2 findings F-001 through F-003
    F-001 (High): Fix environment-corruption bug in dashboard time-range handler
    - Line 3514: Change findIndex predicate from 'env => env.name === env.name'
    (which always returns 0) to 'e => e.name === env.name' (correctly matches
    active environment)
    - Prevents time-range changes from overwriting the first environment's config
    F-002 (Medium): Fix metric query pagination to fetch up to 10 pages per node
2026-06-17 Fix code review round 3 findings F-001 through F-003
    F-001 (Medium): Variable bindings now use user-facing node IDs
    - fetchActualStateNodes() returns {partitionKey, nodeId} where nodeId is
    operator-facing (row.node_id), not internal partition key
    - fetchVariableData() maps nodeId → partitionKey internally for queries
    - Variable table displays user-facing nodeId, not opaque partition keys
    - Edit variable modal validates node selection against discovered nodes
2026-06-18 deps: Bump time from 0.3.47 to 0.3.49 (#1139)
    Bumps [time](https://github.com/time-rs/time) from 0.3.47 to 0.3.49.
    - [Release notes](https://github.com/time-rs/time/releases)
    - [Changelog](https://github.com/time-rs/time/blob/main/CHANGELOG.md)
    - [Commits](https://github.com/time-rs/time/compare/v0.3.47...v0.3.49)
    ---
    updated-dependencies:
2026-06-18 deps: Bump regex from 1.12.3 to 1.12.4 (#1140)
    Bumps [regex](https://github.com/rust-lang/regex) from 1.12.3 to 1.12.4.
    - [Release notes](https://github.com/rust-lang/regex/releases)
    - [Changelog](https://github.com/rust-lang/regex/blob/master/CHANGELOG.md)
    - [Commits](https://github.com/rust-lang/regex/compare/1.12.3...1.12.4)
    ---
    updated-dependencies:
2026-06-18 deps: Bump zeroize from 1.8.2 to 1.9.0 (#1141)
    Bumps [zeroize](https://github.com/RustCrypto/utils) from 1.8.2 to 1.9.0.
    - [Commits](https://github.com/RustCrypto/utils/compare/zeroize-v1.8.2...zeroize-v1.9.0)
    ---
    updated-dependencies:
    - dependency-name: zeroize
    dependency-version: 1.9.0
2026-06-24 ci: Bump actions/checkout from 6.0.3 to 7.0.0
    Bumps [actions/checkout](https://github.com/actions/checkout) from 6.0.3 to 7.0.0.
    - [Release notes](https://github.com/actions/checkout/releases)
    - [Changelog](https://github.com/actions/checkout/blob/main/CHANGELOG.md)
    - [Commits](https://github.com/actions/checkout/compare/df4cb1c069e1874edd31b4311f1884172cec0e10...9c091bb21b7c1c1d1991bb908d89e4e9dddfe3e0)
    ---
    updated-dependencies:
2026-06-24 ci: Bump actions/setup-python from 6.2.0 to 6.3.0
    Bumps [actions/setup-python](https://github.com/actions/setup-python) from 6.2.0 to 6.3.0.
    - [Release notes](https://github.com/actions/setup-python/releases)
    - [Commits](https://github.com/actions/setup-python/compare/a309ff8b426b58ec0e2a45f0f869d46889d02405...ece7cb06caefa5fff74198d8649806c4678c61a1)
    ---
    updated-dependencies:
    - dependency-name: actions/setup-python
2026-06-24 deps: Bump esp32-nimble from `4359528` to `f60d7c5`
    Bumps [esp32-nimble](https://github.com/taks/esp32-nimble) from `4359528` to `f60d7c5`.
    - [Release notes](https://github.com/taks/esp32-nimble/releases)
    - [Commits](https://github.com/taks/esp32-nimble/compare/43595280b3b573ee8a855cf28a0704ecdbd14c60...f60d7c5f41873cdf37579655e8b1c31d78cc3cdd)
    ---
    updated-dependencies:
    - dependency-name: esp32-nimble
2026-06-24 deps: Bump object from 0.36.7 to 0.39.1
    Bumps [object](https://github.com/gimli-rs/object) from 0.36.7 to 0.39.1.
    - [Changelog](https://github.com/gimli-rs/object/blob/main/CHANGELOG.md)
    - [Commits](https://github.com/gimli-rs/object/compare/0.36.7...v0.39.1)
    ---
    updated-dependencies:
    - dependency-name: object
2026-06-24 deps: Bump getrandom from 0.4.2 to 0.4.3
    Bumps [getrandom](https://github.com/rust-random/getrandom) from 0.4.2 to 0.4.3.
    - [Changelog](https://github.com/rust-random/getrandom/blob/master/CHANGELOG.md)
    - [Commits](https://github.com/rust-random/getrandom/compare/v0.4.2...v0.4.3)
    ---
    updated-dependencies:
    - dependency-name: getrandom
2026-06-24 ci: Bump actions/cache from 5.0.5 to 6.0.0 (#1172)
    Bumps [actions/cache](https://github.com/actions/cache) from 5.0.5 to 6.0.0.
    - [Release notes](https://github.com/actions/cache/releases)
    - [Changelog](https://github.com/actions/cache/blob/main/RELEASES.md)
    - [Commits](https://github.com/actions/cache/compare/27d5ce7f107fe9357f9df03efb73ab90386fccae...2c8a9bd7457de244a408f35966fab2fb45fda9c8)
    ---
    updated-dependencies:
2026-06-24 ci: Bump actions/checkout from 6.0.3 to 7.0.0 (#1173)
    Bumps [actions/checkout](https://github.com/actions/checkout) from 6.0.3 to 7.0.0.
    - [Release notes](https://github.com/actions/checkout/releases)
    - [Changelog](https://github.com/actions/checkout/blob/main/CHANGELOG.md)
    - [Commits](https://github.com/actions/checkout/compare/df4cb1c069e1874edd31b4311f1884172cec0e10...9c091bb21b7c1c1d1991bb908d89e4e9dddfe3e0)
    ---
    updated-dependencies:
2026-06-24 ci: Bump actions/setup-python from 6.2.0 to 6.3.0 (#1174)
    Bumps [actions/setup-python](https://github.com/actions/setup-python) from 6.2.0 to 6.3.0.
    - [Release notes](https://github.com/actions/setup-python/releases)
    - [Commits](https://github.com/actions/setup-python/compare/a309ff8b426b58ec0e2a45f0f869d46889d02405...ece7cb06caefa5fff74198d8649806c4678c61a1)
    ---
    updated-dependencies:
    - dependency-name: actions/setup-python
2026-06-24 deps: Bump esp32-nimble from `4359528` to `f60d7c5` (#1175)
    Bumps [esp32-nimble](https://github.com/taks/esp32-nimble) from `4359528` to `f60d7c5`.
    - [Release notes](https://github.com/taks/esp32-nimble/releases)
    - [Commits](https://github.com/taks/esp32-nimble/compare/43595280b3b573ee8a855cf28a0704ecdbd14c60...f60d7c5f41873cdf37579655e8b1c31d78cc3cdd)
    ---
    updated-dependencies:
    - dependency-name: esp32-nimble
2026-06-24 deps: Bump time from 0.3.49 to 0.3.51 (#1177)
    Bumps [time](https://github.com/time-rs/time) from 0.3.49 to 0.3.51.
    - [Release notes](https://github.com/time-rs/time/releases)
    - [Changelog](https://github.com/time-rs/time/blob/main/CHANGELOG.md)
    - [Commits](https://github.com/time-rs/time/compare/v0.3.49...v0.3.51)
    ---
    updated-dependencies:
